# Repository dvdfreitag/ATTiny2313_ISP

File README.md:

ATTiny_ISP
==========

The related documents for my ATTiny2313 ISP project.

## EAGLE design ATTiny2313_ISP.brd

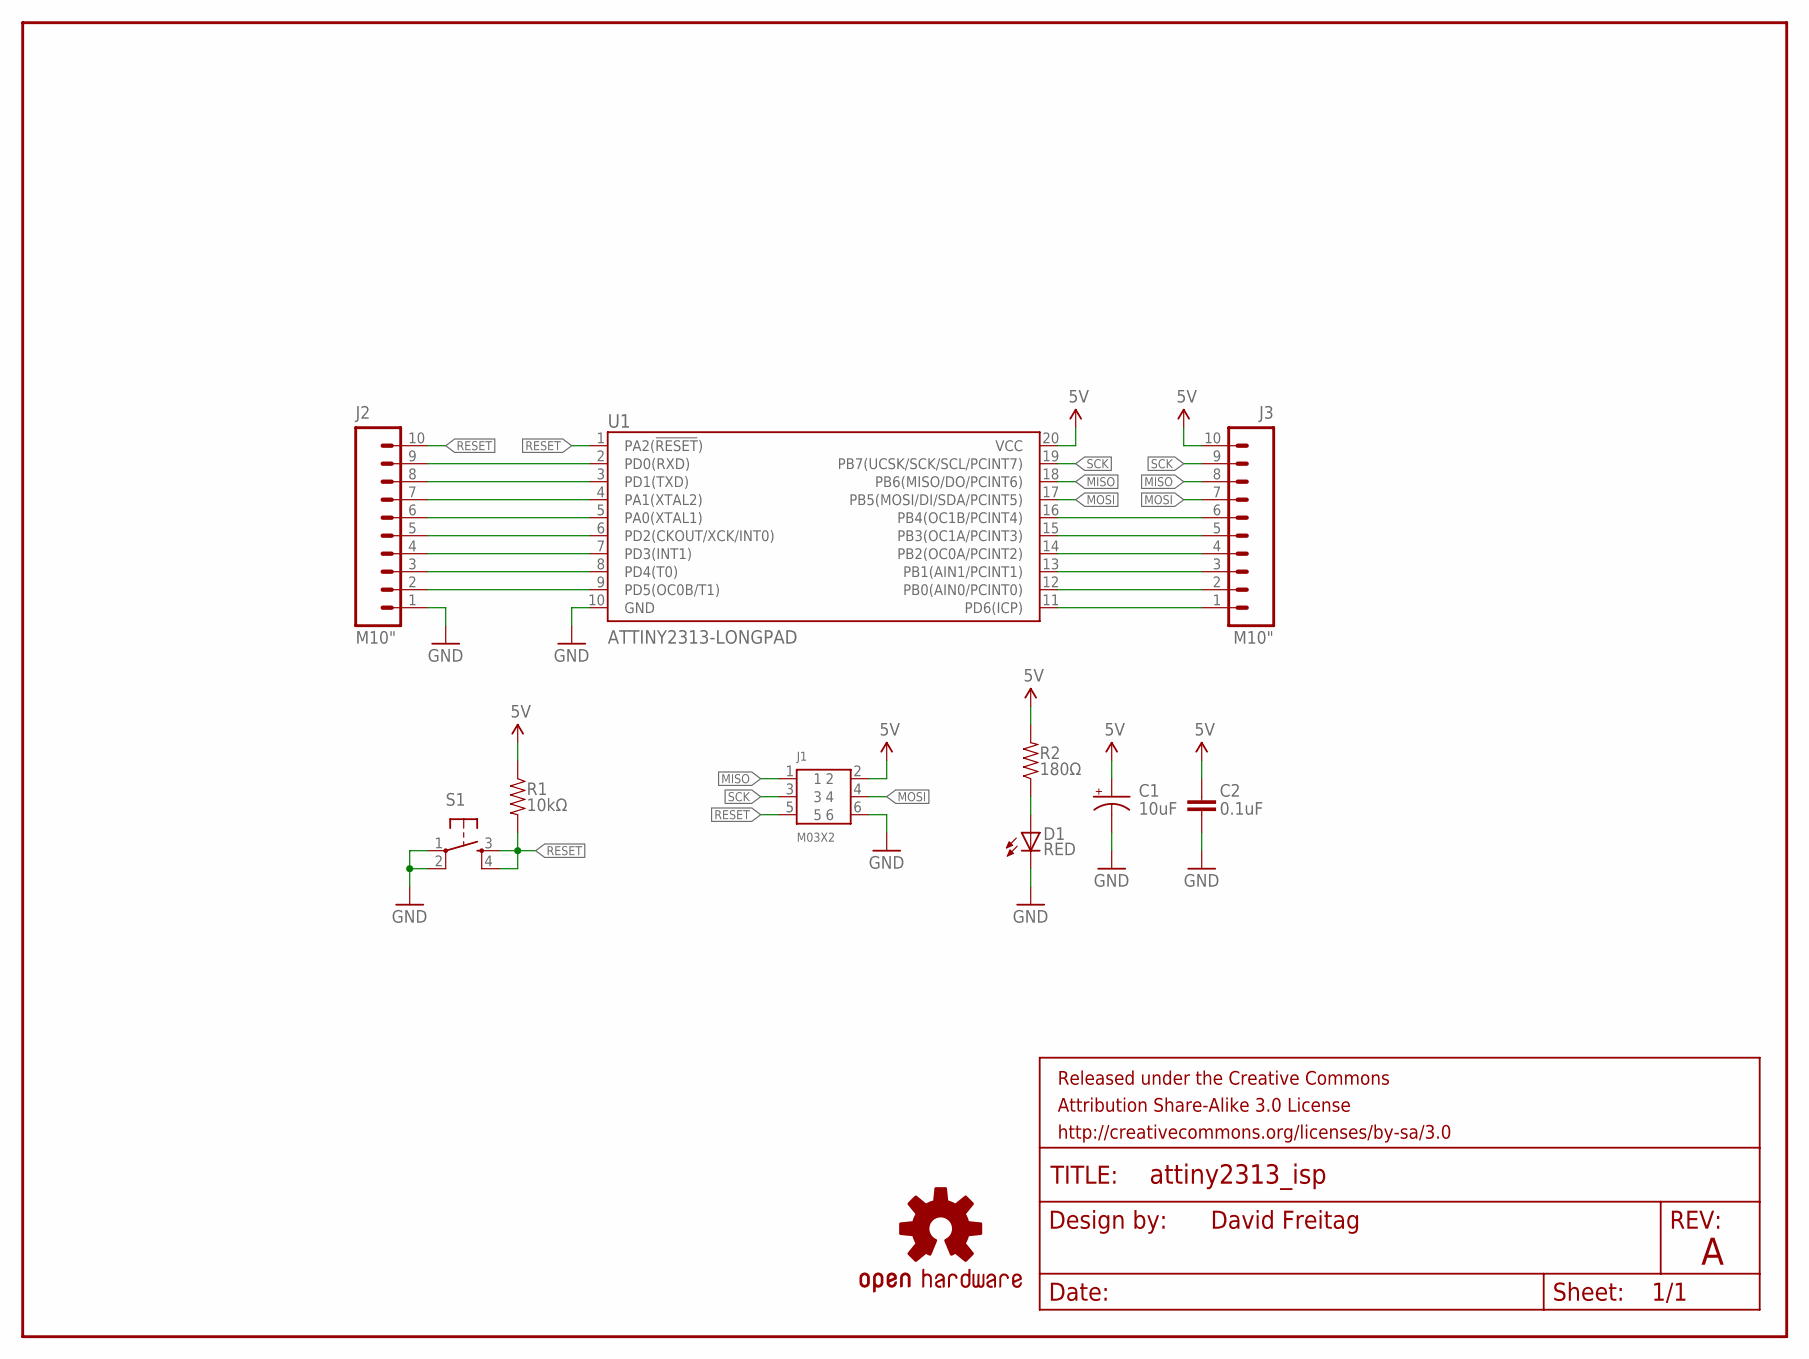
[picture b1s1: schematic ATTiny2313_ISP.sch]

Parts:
C1: 10uF; CPOL-RADIAL-10UF-25V
C2: 0.1uF; CAP-PTH-SMALLEZ
D1: RED; LED3MM
FRAME1: FRAME-LETTER; CREATIVE_COMMONS
J1: M03X2
J2, J3: M10"; 1X10
LOGO1: OSHW-LOGOM; OSHW-LOGO-M
R1: 10kΩ; AXIAL-0.2
R2: 180Ω; AXIAL-0.2
S1: TAC_SWITCHPTH; TACTILE-PTH
U1: ATTINY2313-LONGPAD; DIP20-LONGPAD

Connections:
5V: C1.1 (+), C2.1, J1.2, J3.10, R1.P$1 (1), R2.P$2 (2), U1.20 (VCC)
GND: C1.2 (-), C2.2, D1.K (C), J1.6, J2.1, S1.1, S1.2, U1.10 (GND)
MISO: J1.1, J3.8, U1.18 (PB6(MISO/DO/PCINT6))
MOSI: J1.4, J3.7, U1.17 (PB5(MOSI/DI/SDA/PCINT5))
unnamed: D1.A, R2.P$1 (1)
unnamed: J2.9, U1.2 (PD0(RXD))
unnamed: J2.8, U1.3 (PD1(TXD))
unnamed: J2.7, U1.4 (PA1(XTAL2))
unnamed: J2.6, U1.5 (PA0(XTAL1))
unnamed: J2.5, U1.6 (PD2(CKOUT/XCK/INT0))
unnamed: J2.4, U1.7 (PD3(INT1))
unnamed: J2.3, U1.8 (PD4(T0))
unnamed: J2.2, U1.9 (PD5(OC0B/T1))
unnamed: J3.6, U1.16 (PB4(OC1B/PCINT4))
unnamed: J3.5, U1.15 (PB3(OC1A/PCINT3))
unnamed: J3.4, U1.14 (PB2(OC0A/PCINT2))
unnamed: J3.3, U1.13 (PB1(AIN1/PCINT1))
unnamed: J3.2, U1.12 (PB0(AIN0/PCINT0))
unnamed: J3.1, U1.11 (PD6(ICP))
RESET: J1.5, J2.10, R1.P$2 (2), S1.3, S1.4, U1.1 (PA2(!RESET!))
SCK: J1.3, J3.9, U1.19 (PB7(UCSK/SCK/SCL/PCINT7))

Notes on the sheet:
David Freitag

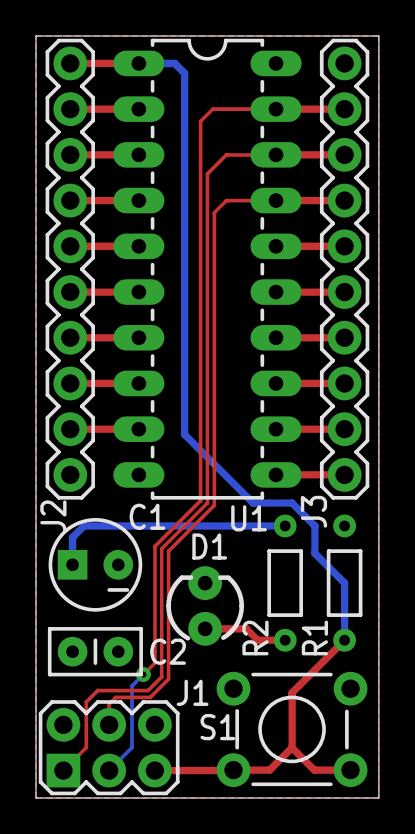
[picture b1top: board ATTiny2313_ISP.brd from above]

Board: 2 copper layers, 19.1 x 42.3 mm, 12 parts (1 on the bottom side), 21 nets.

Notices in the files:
parts and their libraries:
SparkFun-Electromechanical: Licensing: CC v3.0 Share-Alike You are welcome to use this library for commercial purposes.
SparkFun-Aesthetics: Released under the Creative Commons Attribution Share-Alike 3.0 License
SparkFun-Aesthetics: http://creativecommons.org/licenses/by-sa/3.0
